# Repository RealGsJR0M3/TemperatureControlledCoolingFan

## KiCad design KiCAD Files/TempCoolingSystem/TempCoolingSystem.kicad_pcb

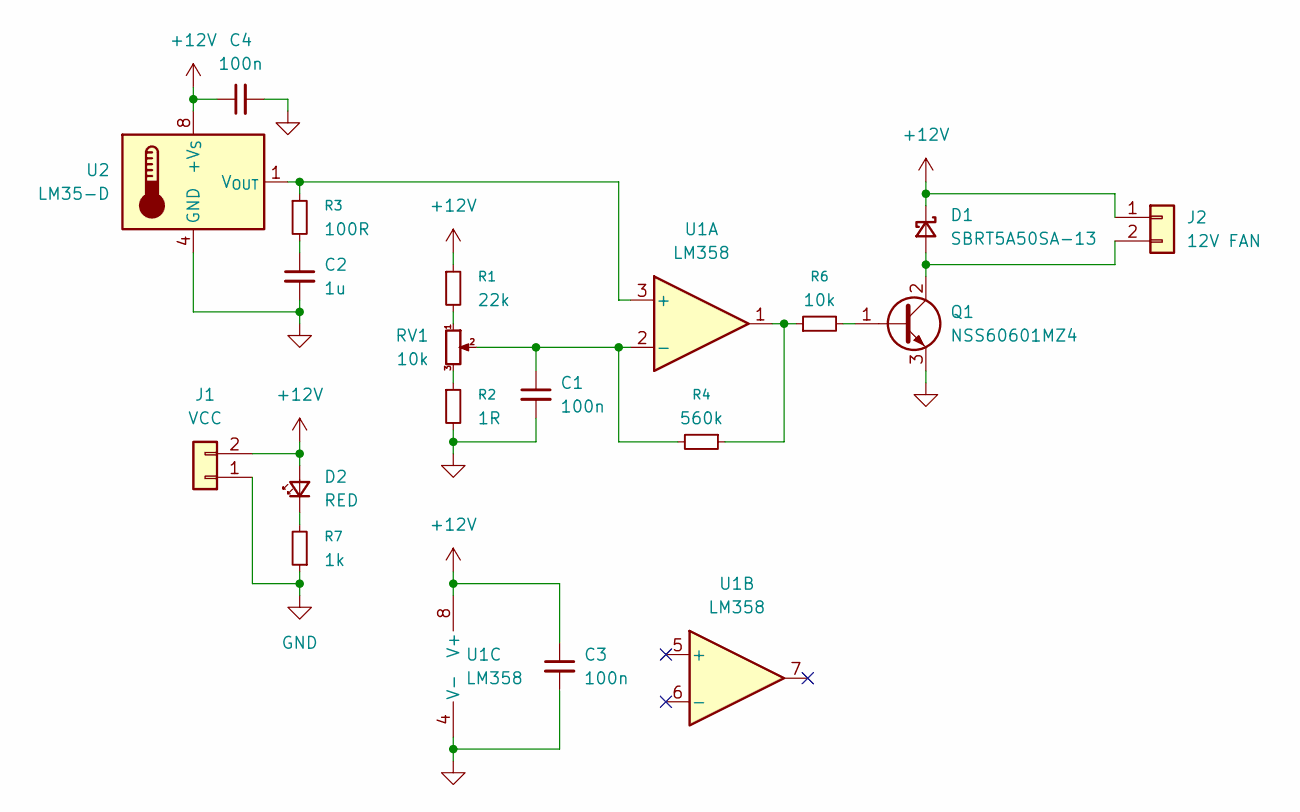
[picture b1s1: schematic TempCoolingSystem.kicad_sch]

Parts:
C1, C3, C4: 100n; C_0805_2012Metric_Pad1.18x1.45mm_HandSolder
C2: 1u; C_0805_2012Metric_Pad1.18x1.45mm_HandSolder
D1: SBRT5A50SA-13; D_SMA
D2: RED; LED_0805_2012Metric_Pad1.15x1.40mm_HandSolder
J1: VCC; PinHeader_1x02_P2.54mm_Vertical
J2: 12V FAN; PinHeader_1x02_P2.54mm_Vertical
Q1: NSS60601MZ4; SOT-223-3_TabPin2
R1: 22k; R_0805_2012Metric_Pad1.20x1.40mm_HandSolder
R2: 1R; R_0805_2012Metric_Pad1.20x1.40mm_HandSolder
R3: 100R; R_0805_2012Metric_Pad1.20x1.40mm_HandSolder
R4: 560k; R_0805_2012Metric_Pad1.20x1.40mm_HandSolder
R6: 10k; R_0805_2012Metric_Pad1.20x1.40mm_HandSolder
R7: 1k; R_0805_2012Metric_Pad1.20x1.40mm_HandSolder
RV1: 10k; Potentiometer_Bourns_3296W_Vertical
U1: LM358; SOIC-8_3.9x4.9mm_P1.27mm
U2: LM35-D; SOIC-8_3.9x4.9mm_P1.27mm

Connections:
+12V: C3.1, C4.1, D1.1 (K), D2.2 (A), J1.2, J2.1, R1.1, U1.8 (V+), U2.8 (+V_{S})
GND: C1.2, C2.2, C3.2, C4.2, J1.1, Q1.3 (E), R2.2, R7.1, U1.4 (V-), U2.4 (GND)
unnamed: C2.1, R3.2
unnamed: D1.2 (A), J2.2, Q1.2 (C)
unnamed: D2.1 (K), R7.2
unnamed: Q1.1 (B), R6.2
unnamed: R1.2, RV1.1
unnamed: R2.1, RV1.3
unnamed: R4.1, R6.1, U1.1
unnamed: R3.1, U1.3 (+), U2.1 (V_{OUT})
unnamed: C1.1, R4.2, RV1.2, U1.2 (-)

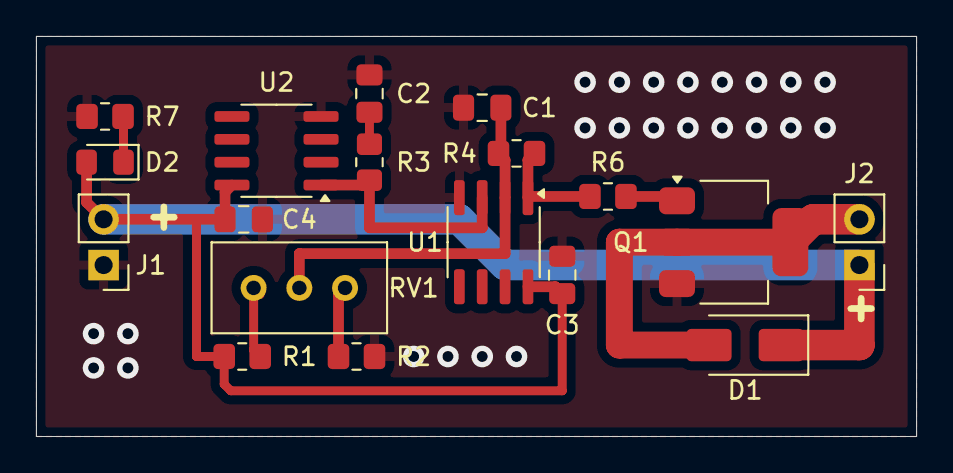
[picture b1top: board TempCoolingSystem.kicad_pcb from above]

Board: 2 copper layers, 48.9 x 22.2 mm, 18 parts (0 on the bottom side), 11 nets.

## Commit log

2025-05-13 Schematic & PCB Layout
